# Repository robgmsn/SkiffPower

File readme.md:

DESIGN STATUS: Awaiting Testing - Ready for beta testing

Skiff Power Updated to V1.1 24/4/21

Added 5V
Changed footprints to SMD to save space
Rerouted all

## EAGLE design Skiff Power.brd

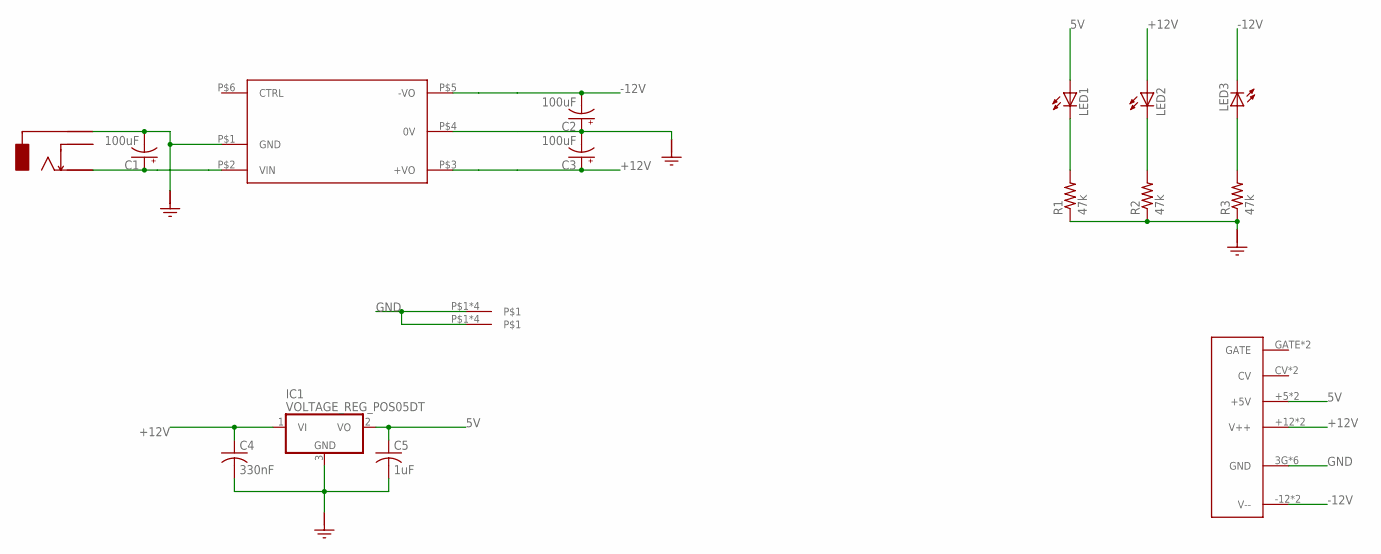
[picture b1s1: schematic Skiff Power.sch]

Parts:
C1, C2, C3: 100uF; SANYO-OSCON_D
C4: 330nF; C0805
C5: 1uF; C0805
IC1: VOLTAGE_REG_POS05DT; TO252
LED1, LED2, LED3: LED3MM
R1, R2, R3: 47k; R0805
U$1: URA241XLD-20WR3
U$2: SOCKET_DC_POWER; DC-POWER
U$3: EURO_POWER_16; POWER_SHROUDED
U$10, U$11: PCBMOUNT; PCB-2-MOUNTING

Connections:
5V: C5.1, IC1.2 (VO), LED1.A, U$3.+5 (+5V), U$3.+5A (+5V)
+12V: C3.+, C4.1, IC1.1 (VI), LED2.A, U$1.P$3 (+VO), U$3.+12 (V++), U$3.+12A (V++)
-12V: C2.-, LED3.K (C), U$1.P$5 (-VO), U$3.-12 (V--), U$3.-12A (V--)
GND: C1.-, C2.+, C3.-, C4.2, C5.2, IC1.3 (GND), R1.1, R2.1, R3.1, U$1.P$1 (GND), U$1.P$4 (0V), U$2.SLEEVEBOT (SLEEVE), U$2.SLEEVETOP (SLEEVE), U$3.3G (GND), U$3.4G (GND), U$3.5G (GND), U$3.6G (GND), U$3.7G (GND), U$3.8G (GND), U$10.P$1, U$10.P$2, U$10.P$3, U$10.P$4, U$11.P$1, U$11.P$2, U$11.P$3, U$11.P$4
unnamed: LED1.K (C), R1.2
unnamed: C1.+, U$1.P$2 (VIN), U$2.PINBOT (PIN), U$2.PINTOP (PIN)
unnamed: LED2.K (C), R2.2
unnamed: LED3.A, R3.2

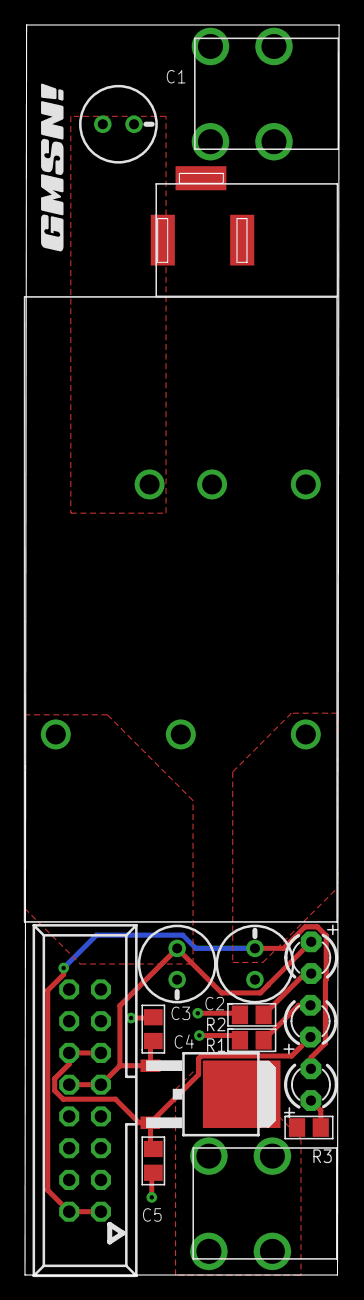
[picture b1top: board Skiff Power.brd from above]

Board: 2 copper layers, 25.1 x 100.0 mm, 19 parts (1 on the bottom side), 8 nets.

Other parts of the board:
U$4, U$5: GMSN!_LOGO

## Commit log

2021-04-25 Skiff Power 1.1
    Added 5V
    Changed footprints to SMD to save space
    Rerouted all
2021-07-07 Reinstall

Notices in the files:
Skiff Power.brd:
cc-by 4.0 2021
